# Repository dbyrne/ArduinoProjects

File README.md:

A collection of some simple Arduino projects.

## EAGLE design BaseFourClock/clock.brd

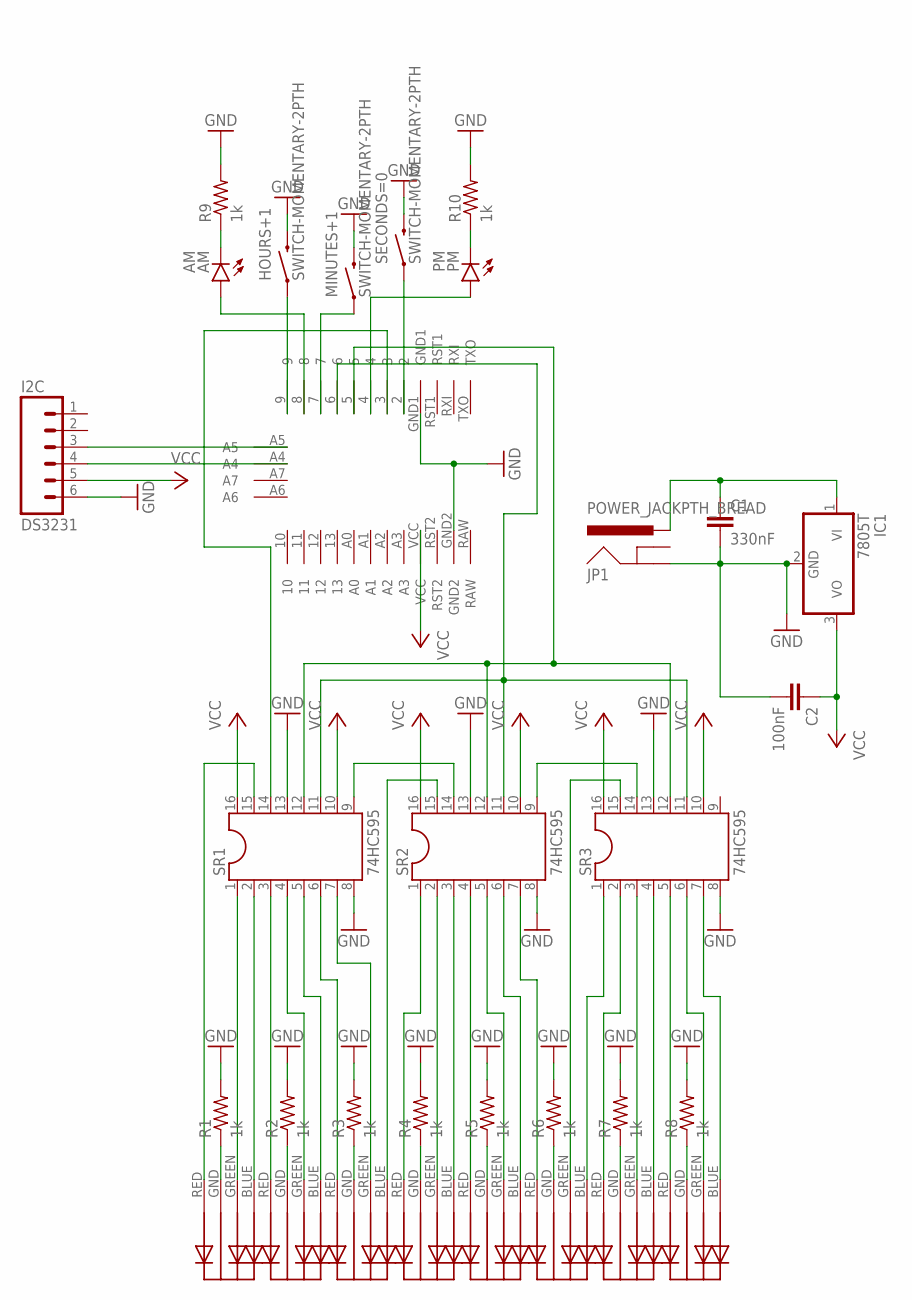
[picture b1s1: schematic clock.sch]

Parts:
AM: AM; LED5MM
C1: 330nF; CAP-PTH-5MM
C2: 100nF; CAP-PTH-5MM
DS3231: I2C; 1X06_LOCK
HOURS+1: SWITCH-MOMENTARY-2PTH; TACTILE-PTH
IC1: 7805T; TO220V
JP1: POWER_JACKPTH_BREAD; POWER_JACK_PTH_BREAD
MINUTES+1: SWITCH-MOMENTARY-2PTH; TACTILE-PTH
PM: PM; LED5MM
R1, R2, R3, R4, R5, R6, R7, R8, R9, R10: 1k; 0207/10
SECONDS=0: SWITCH-MOMENTARY-2PTH; TACTILE-PTH
SR1, SR2, SR3: 74HC595; SOCKET-16
U$1: PRO-MINI
U$2, U$3, U$4, U$5, U$6, U$7, U$8, U$9: RGB_LED_COM_CATH

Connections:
GND: C1.2, C2.2, DS3231.6, HOURS+1.3 (2), IC1.2 (GND), JP1.GND, MINUTES+1.3 (2), R1.2, R2.2, R3.2, R4.2, R5.2, R6.2, R7.2, R8.2, R9.2, R10.2, SECONDS=0.3 (2), SR1.8, SR1.13, SR2.8, SR2.13, SR3.8, SR3.13, U$1.GND1, U$1.GND2
unnamed: SR1.6, U$2.RED
unnamed: SR1.9, SR2.14
unnamed: SR2.9, SR3.14
unnamed: SR1.11, SR2.11, SR3.11, U$1.6
unnamed: SR1.12, SR2.12, SR3.12, U$1.5
unnamed: SR1.14, U$1.3
unnamed: SR1.15, U$4.RED
unnamed: SR1.1, U$4.GREEN
unnamed: SR1.2, U$4.BLUE
unnamed: R1.1, U$4.GND
unnamed: SR1.3, U$3.RED
unnamed: SR1.4, U$3.GREEN
unnamed: SR1.5, U$3.BLUE
unnamed: R2.1, U$3.GND
unnamed: SR1.7, U$2.GREEN
unnamed: SR2.15, U$2.BLUE
unnamed: R3.1, U$2.GND
unnamed: R4.1, U$5.GND
unnamed: SR2.1, U$5.RED
unnamed: SR2.2, U$5.GREEN
unnamed: SR2.3, U$5.BLUE
unnamed: SR2.4, U$6.RED
unnamed: SR2.5, U$6.GREEN
unnamed: SR2.6, U$6.BLUE
unnamed: R5.1, U$6.GND
unnamed: SR2.7, U$7.RED
unnamed: R6.1, U$7.GND
unnamed: SR3.3, U$8.GREEN
unnamed: SR3.1, U$7.BLUE
unnamed: SR3.15, U$7.GREEN
unnamed: R7.1, U$8.GND
unnamed: SR3.2, U$8.RED
unnamed: SR3.4, U$8.BLUE
unnamed: SR3.5, U$9.RED
unnamed: R8.1, U$9.GND
unnamed: SR3.6, U$9.GREEN
unnamed: SR3.7, U$9.BLUE
unnamed: DS3231.3, U$1.A5
unnamed: DS3231.4, U$1.A4
unnamed: HOURS+1.1, U$1.9
unnamed: AM.A, U$1.8
unnamed: MINUTES+1.1, U$1.7
unnamed: PM.A, U$1.4
unnamed: SECONDS=0.1, U$1.2
unnamed: AM.K (C), R9.1
unnamed: PM.K (C), R10.1
unnamed: C1.1, IC1.1 (VI), JP1.PWR
VCC: C2.1, DS3231.5, IC1.3 (VO), SR1.10, SR1.16, SR2.10, SR2.16, SR3.10, SR3.16, U$1.VCC

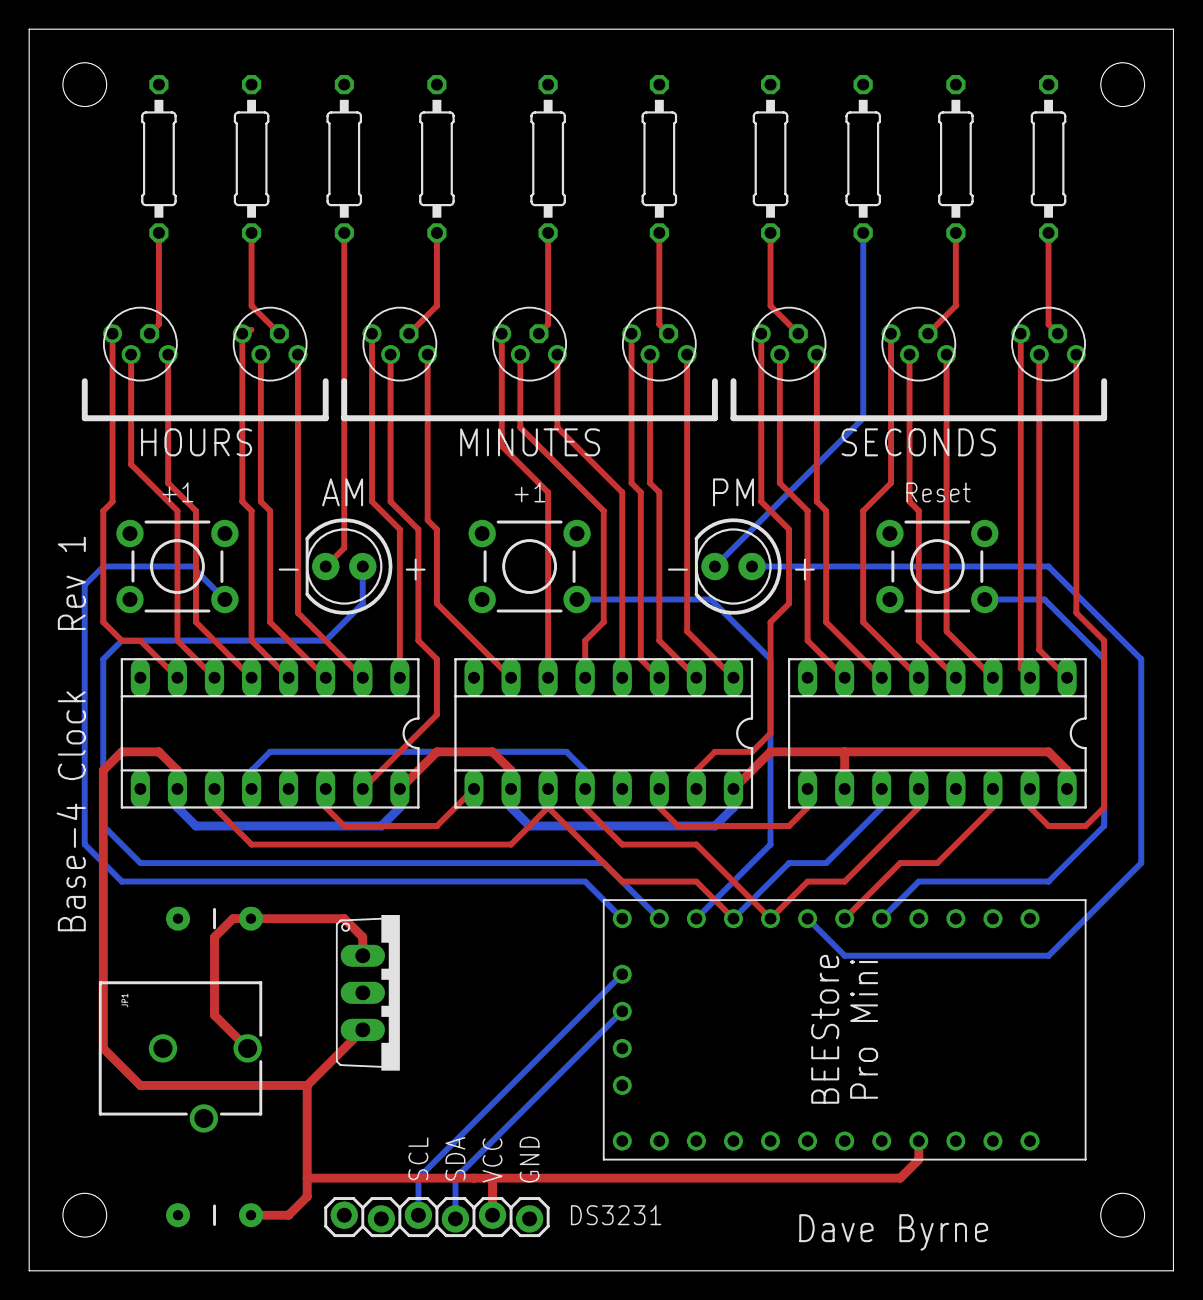
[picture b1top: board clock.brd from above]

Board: 2 copper layers, 78.4 x 85.1 mm, 32 parts (0 on the bottom side), 49 nets.

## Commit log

2014-12-01 Doorbell project added
2014-12-01 added spiderman theme
2014-12-04 Trinket Doorbell Added
2014-12-07 Optical theremin project added
2014-12-08 Dice code added
2014-12-13 Dice project completed
2014-12-13 Doc Ock claws project added
2014-12-14 added a second servo
2014-12-15 go board project added
2014-12-20 temp OLED project added
2014-12-21 LED Cube project added
2015-01-03 Compass project added
2015-01-05 Astable multivibrator circuit
2015-01-05 schematic tweak
2015-01-10 Volt meter project
2015-01-12 updated code
2015-02-10 base-4 clock project

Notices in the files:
parts and their libraries:
SparkFun-Connectors: Licensing: Creative Commons ShareAlike 4.0 International - https://creativecommons.org/licenses/by-sa/4.0
